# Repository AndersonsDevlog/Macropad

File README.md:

# Macropad

A custom 12-key macropad with **2 rotary encoders** and **per-key RGB LED lighting**, designed in KiCad as a compact USB HID device for shortcuts, media control, and creative workflows.
---

## Features

- **12 mechanical key switches** in a 4x3 matrix ([hot-swap / solder])
- **2 rotary encoders** with push buttons (volume, scrolling, zoom, etc.)
- **RGB LED lighting** ([SK6812MINI-E / WS2812B], addressable)
- **USB-C** for power and data
- **[MCU]** microcontroller ([RP2040 / STM32 / ATmega32U4])
- **3D view** (`Macropad.stl`)
- Firmware: [QMK / KMK / CircuitPython]

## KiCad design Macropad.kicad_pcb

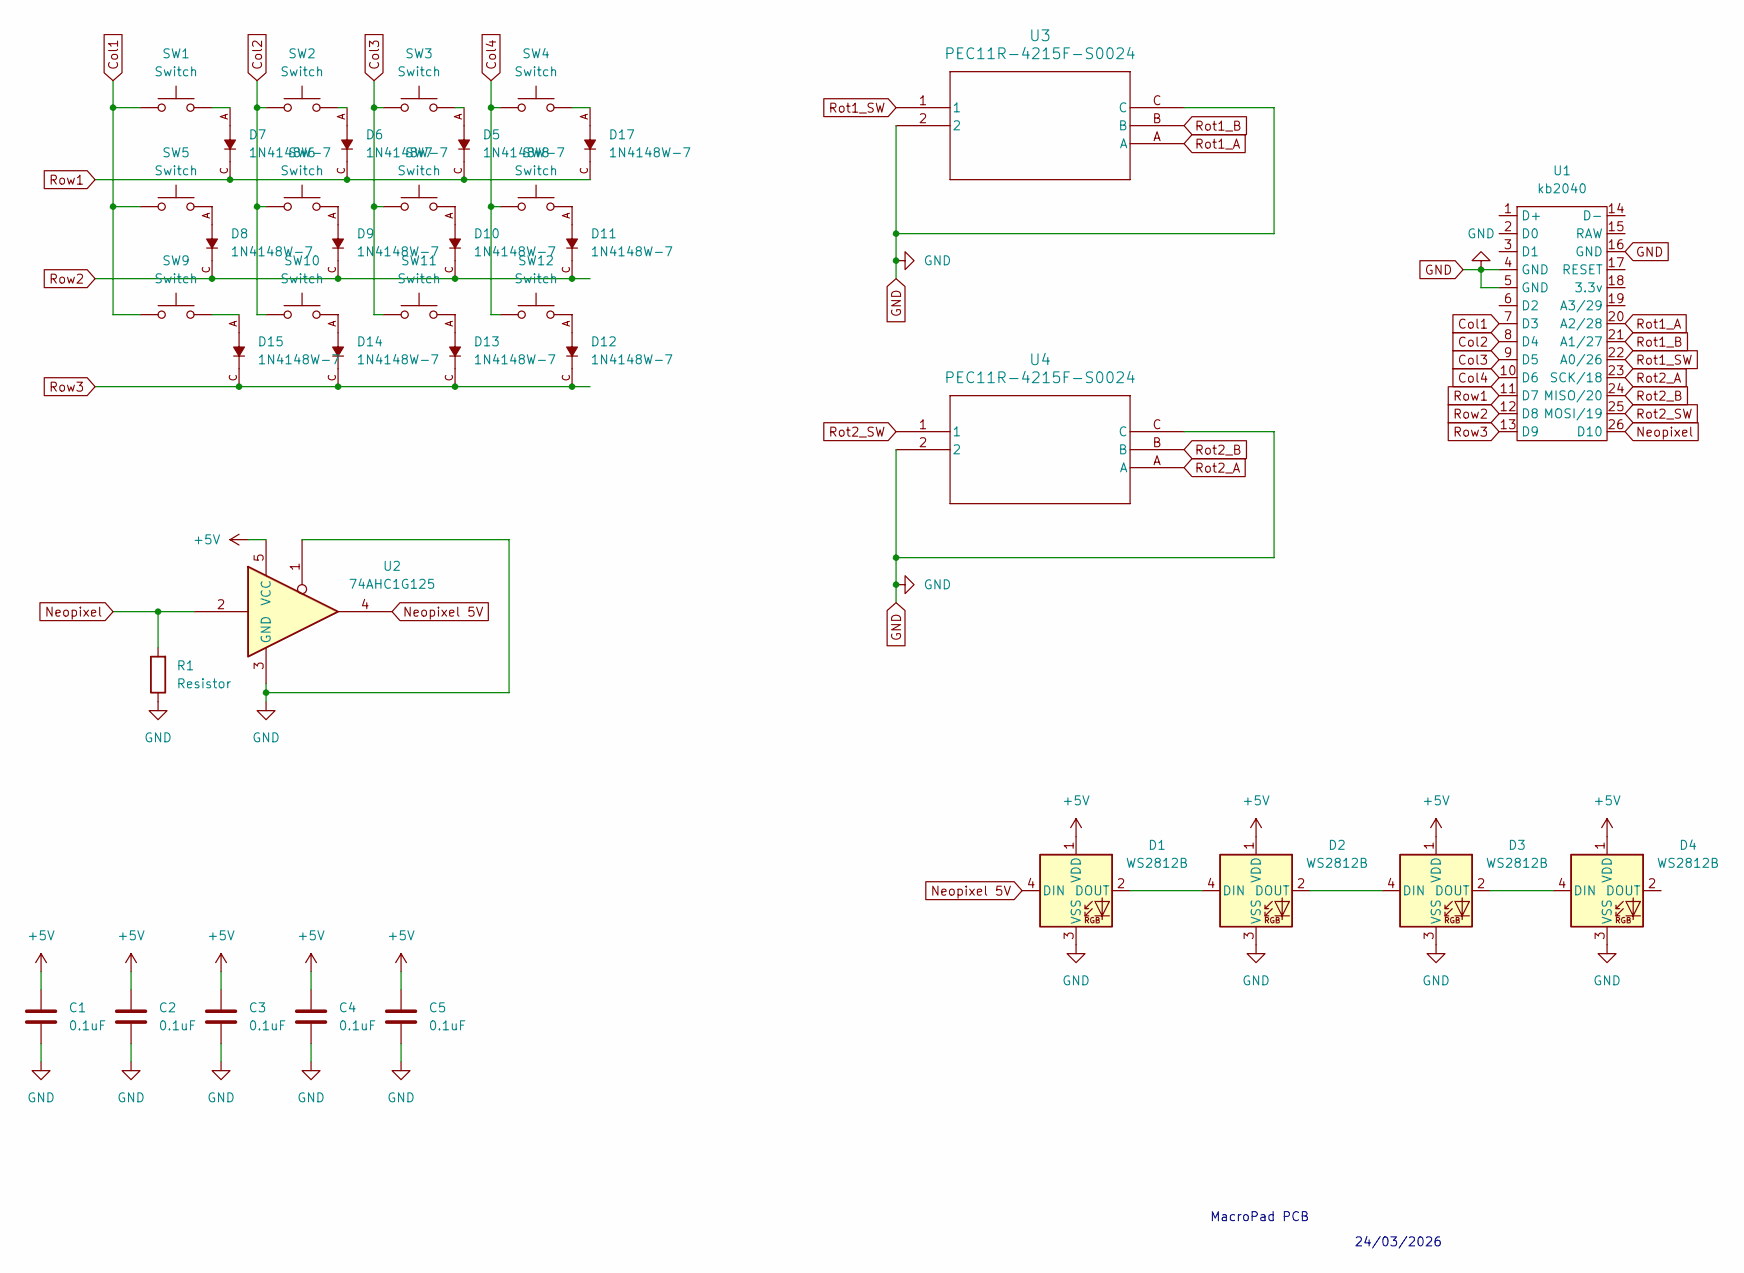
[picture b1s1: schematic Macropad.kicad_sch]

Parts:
C1, C2, C3, C4, C5: 0.1uF; CAP_CL10_SAM
D1, D2, D3, D4: WS2812B; LED_WS2812B_PLCC4_5.0x5.0mm_P3.2mm
D5, D6, D7, D8, D9, D10, D11, D12, D13, D14, D15, D17: 1N4148W-7; SOD3715X135N; PARTREV 28-2
R1: Resistor; RES_RMCF0805_STP
SW1, SW2, SW3, SW4, SW5, SW6, SW7, SW8, SW9, SW10, SW11, SW12: Switch; SW_Cherry_MX_1.00u_PCB
U1: kb2040
U2: 74AHC1G125; DBV5
U3, U4: PEC11R-4215F-S0024; TO_215F-S0024

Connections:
+5V: C1.1, C2.1, C3.1, C4.1, C5.1, D1.1 (VDD), D2.1 (VDD), D3.1 (VDD), D4.1 (VDD), U2.5 (VCC)
Col1: SW1.1, SW5.1, SW9.1, U1.7 (D3)
Col2: SW2.1, SW6.1, SW10.1, U1.8 (D4)
Col3: SW3.1, SW7.1, SW11.1, U1.9 (D5)
Col4: SW4.1, SW8.1, SW12.1, U1.10 (D6)
GND: C1.2, C2.2, C3.2, C4.2, C5.2, D1.3 (VSS), D2.3 (VSS), D3.3 (VSS), D4.3 (VSS), R1.1, U1.4 (GND), U1.5 (GND), U1.16 (GND), U2.1, U2.3 (GND), U3.2, U3.C, U4.2, U4.C
Neopixel: R1.2, U1.26 (D10), U2.2
Neopixel 5V: D1.4 (DIN), U2.4
unnamed: D1.2 (DOUT), D2.4 (DIN)
unnamed: D2.2 (DOUT), D3.4 (DIN)
unnamed: D3.2 (DOUT), D4.4 (DIN)
unnamed: D5.A, SW3.2
unnamed: D6.A, SW2.2
unnamed: D7.A, SW1.2
unnamed: D8.A, SW5.2
unnamed: D9.A, SW6.2
unnamed: D10.A, SW7.2
unnamed: D11.A, SW8.2
unnamed: D12.A, SW12.2
unnamed: D13.A, SW11.2
unnamed: D14.A, SW10.2
unnamed: D15.A, SW9.2
unnamed: D17.A, SW4.2
Rot1_A: U1.20 (A2/28), U3.A
Rot1_B: U1.21 (A1/27), U3.B
Rot1_SW: U1.22 (A0/26), U3.1
Rot2_A: U1.23 (SCK/18), U4.A
Rot2_B: U1.24 (MISO/20), U4.B
Rot2_SW: U1.25 (MOSI/19), U4.1
Row1: D5.C, D6.C, D7.C, D17.C, U1.11 (D7)
Row2: D8.C, D9.C, D10.C, D11.C, U1.12 (D8)
Row3: D12.C, D13.C, D14.C, D15.C, U1.13 (D9)

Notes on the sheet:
MacroPad PCB
24/03/2026

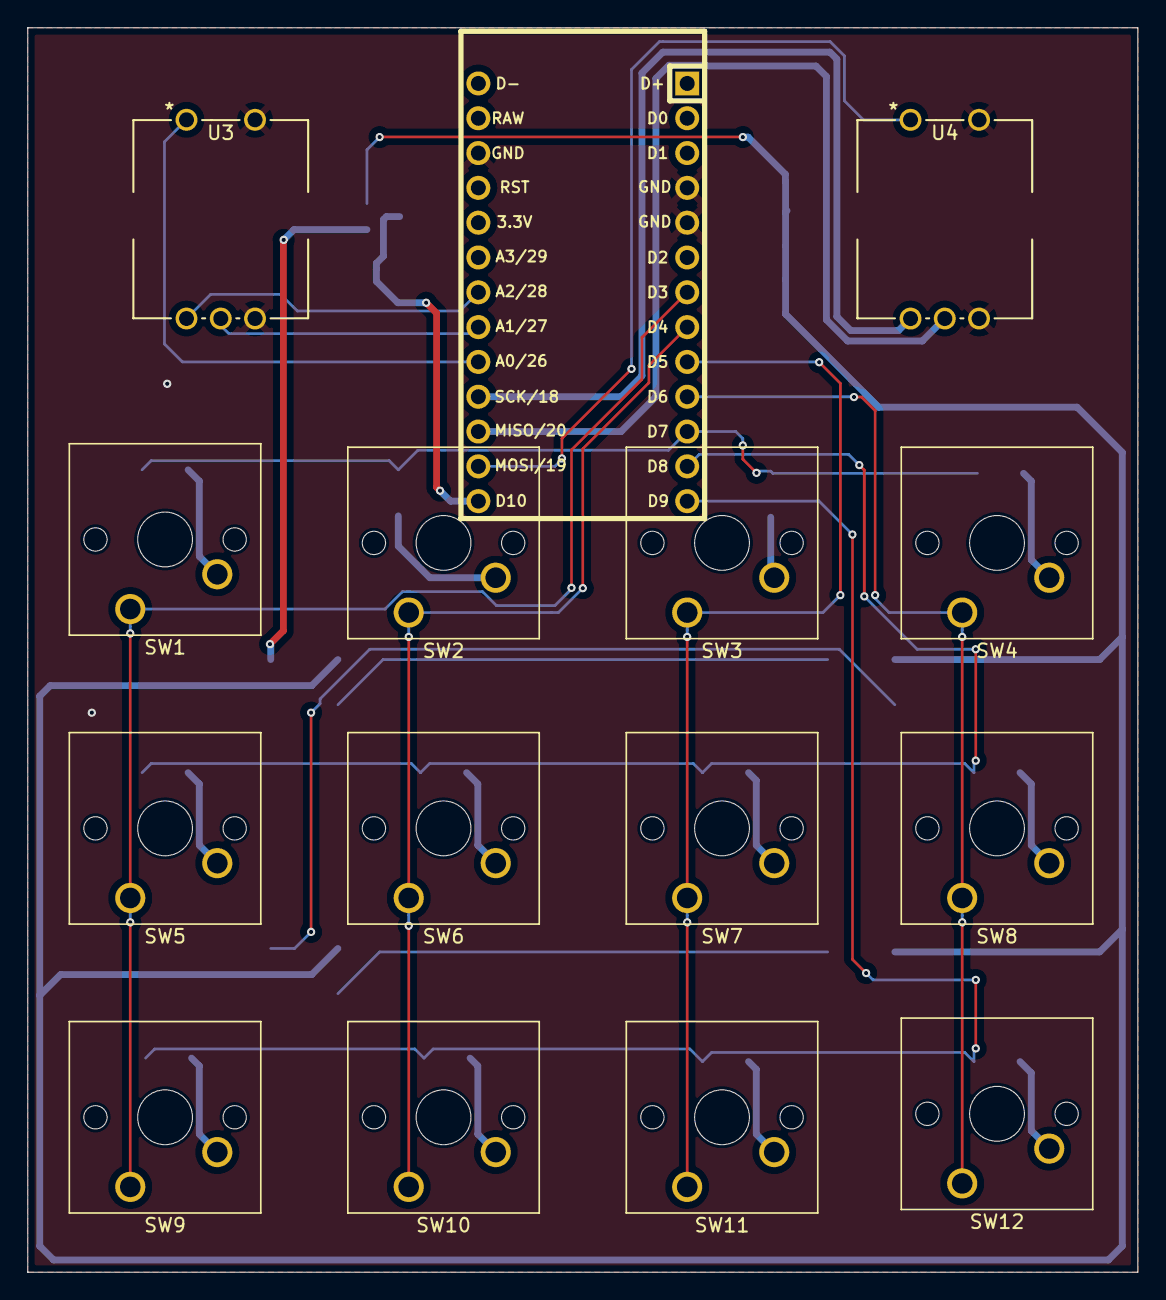
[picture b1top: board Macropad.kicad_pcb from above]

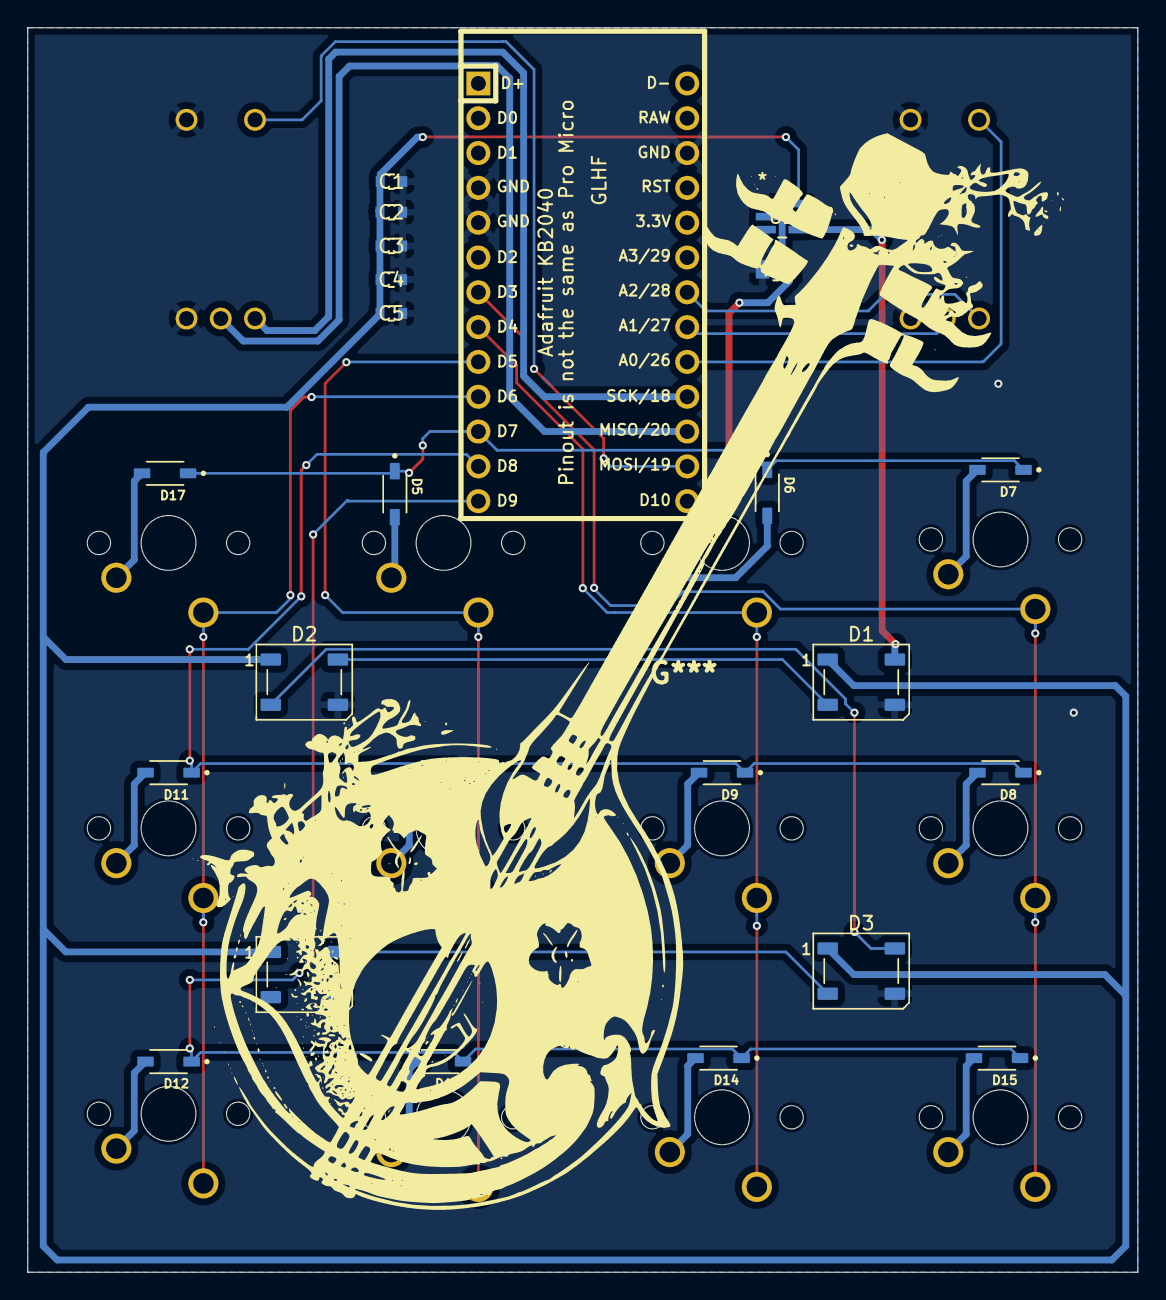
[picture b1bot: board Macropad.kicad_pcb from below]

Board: 2 copper layers, 81.0 x 90.8 mm, 38 parts (24 on the bottom side), 32 nets.
